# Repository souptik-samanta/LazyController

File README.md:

# LazyController

A compact WiFi-enabled relay controller built on a custom PCB. Flip switches, trigger appliances, and automate stuff — all from your phone or browser. No getting up required.

---
BUILD

## What is it?

LazyController is an IoT relay board designed around an ESP-based microcontroller. It exposes relay outputs over WiFi, letting you remotely toggle lights, fans, pumps, or anything else you'd rather not walk over to.

- Custom PCB with onboard relay(s)
- WiFi control via a web interface or serial commands
- Compact form factor — designed to tuck away somewhere tidy
- Production-ready Gerbers included for ordering straight from JLCPCB/PCBWay

---

## Repository Layout

```
LazyController/
├── Cad/          # Enclosure and assembly CAD files
├── Code/         # Firmware source (code.ino)
├── lib/          # README images/assets
├── Pcb/          # KiCad project files (schematic + PCB)
├── production/   # Manufacturing outputs (BOM, positions, netlist, backups)
└── README.md
```

---

## PCB

The board was designed with simplicity in mind — power in, relay out, WiFi in the middle.

> PCB layout and schematic are in the `Pcb/` folder.  
> Gerbers for direct upload to your fab of choice are in `production/`.

Ordering a board:
1. Zip the contents of `production/`
2. Upload to [JLCPCB](https://jlcpcb.com) or [PCBWay](https://www.pcbway.com)
3. Default settings (1.6mm, HASL, FR4) work fine

---
# Schematic

### ESP

<details>
   <summary><strong>USB</strong></summary>
   
</details>

<details>
   <summary><strong>Switching</strong></summary>
   
</details>

<details>
   <summary><strong>ACDC</strong></summary>
   
</details>

<details>
   <summary><strong>POWER</strong></summary>
   
</details>

## Flashing Firmware

> Make sure you have the [Arduino IDE](https://www.arduino.cc/en/software) or [PlatformIO](https://platformio.org) installed.

1. Add ESP32 board support if you haven't already:
   - In Arduino IDE → Preferences → Additional Board URLs:
     ```
     https://espressif.github.io/arduino-esp32/package_esp32_index.json
     ```
2. Install required libraries:
   - `ESPWiFi` (or `WiFi` for ESP32)
   - `ESPAsyncWebServer` *(recommended)*
3. Open your firmware sketch, set your WiFi credentials:
   ```cpp
   const char* ssid     = "your_network";
   const char* password = "your_password";
   ```
4. Select your board, plug in via USB, and hit **Upload**
5. Open Serial Monitor at `115200 baud` — it'll print the device IP once connected

---

## Wiring

```
Power the controller → relays get activated → each relay switches its connected load.
```

Relay outputs are SPDT — connect your load between **COM** and **NO** (normally open) for off-by-default behaviour.

> If switching mains voltage (120V/230V AC), make sure you take appropriate safety precautions. 

---

## Usage

Once flashed and powered:

1. Connect to the same WiFi network
2. Open a browser and navigate to the IP shown in Serial Monitor
3. Toggle relays from the web UI — or send HTTP requests directly:
   ```
   GET /relay/1/on
   GET /relay/1/off
   ```

---

## BOM

| NAME | DESC | QUAN | PRICE (USD) | PRICE TOT | LINK |
| --- | --- | ---: | ---: | ---: | --- |
| AC DC HLK 10M05 |  | 1 | 3 | 3 | [Link](https://www.google.com/aclk?sa=L&ai=DChsSEwjPgJLYkqGTAxU3E3sHHbncDPEYACICCAEQBhoCdG0&co=1&ase=2&gclid=CjwKCAjwjtTNBhB0EiwAuswYhhi3KHJIBAfwGXL-EoLnVRphFNGoqQidNDPKgIrQrcWKpcyjFP1VwBoCSCgQAvD_BwE&cid=CAASugHkaCU4e1fTz91kIGVNTnMzHJ_VtP52cufw6JcAMd-wP2ZSC0BoTFjcM9-ZIEFZ2Ogk6CTtzVucR90V1M1RdjyK8HSMxB6BEAwHAFI-Qtww65Lwu8Fu6KI2zU4457GgK06UIFovm7KTyVTxhy48PClOoNt_d_CozoYxK3R0wXO_8_H_BQkMjDaVLeeHGUlEV7Eb_OuckPo7iFx0EI2Cnf5IhQow1eqdLKqXXLbz55rZELgi1aYbH8s2oEE&cce=2&category=acrcp_v1_32&sig=AOD64_3fvvBr-_NRkMTrQTSOe75uZZv-rw&ctype=5&q=&nis=4&ved=2ahUKEwjd_4nYkqGTAxVSaPUHHT2JI8IQ9aACKAB6BAgLEA8&adurl=) |
| 6 Pin 5.08mm Pitch Pluggable Screw Terminal Block |  | 1 | 1 | 1 | [Link](https://robu.in/product/6-pin-5-08mm-pitch-pluggable-screw-terminal-block-pack-of-3/?gad_source=1&gad_campaignid=17427802703&gbraid=0AAAAADvLFWdwdvSUFSJIl7gt4S3iz58C-&gclid=CjwKCAjwjtTNBhB0EiwAuswYhp7bcND74BjkuenRPwyCr11HA-Sdw3UXYKsvjuJCSPtey4QP6JC4nhoCA68QAvD_BwE) |
| RELAY |  | 4 | 1 | 4 | [Link](https://robu.in/product/srd-5vdc-sl-a-ningbo-songle-relay-250vac-5v-15a-1-form-a-1a-spst-no-plugin15-6x19-2mm-power-relays-rohs/) |
| pcb |  | 23 | 1 | 23 |  |
| LCSC |  |  |  |  |  |
| CC0805JRNPO9BN471 | Description | 100 | 0.0074 | 0.74 | [Link](https://www.lcsc.com/product-detail/C62771.html) |
| CL21A225KBQNNNE | 470pF ±5% 50V Ceramic Capacitor NP0 0805 | 10 | 0.0176 | 0.176 | [Link](https://www.lcsc.com/product-detail/C377773.html) |
| GRM21BR61H106KE43L | 2.2uF ±10% 50V Ceramic Capacitor X5R 0805 | 10 | 0.0723 | 0.723 | [Link](https://www.lcsc.com/product-detail/C440198.html) |
| CC0603KRX7R9BB104 | 10uF ±10% 50V Ceramic Capacitor X5R 0805 | 100 | 0.0028 | 0.28 | [Link](https://www.lcsc.com/product-detail/C14663.html) |
| 1N5819W | 100nF ±10% 50V Ceramic Capacitor X7R 0603 | 100 | 0.0072 | 0.72 | [Link](https://www.lcsc.com/product-detail/C963381.html) |
| TYPE-C 16PIN 2MD(073) | Diode Independent 40V 350mA Surface Mount SOD-123 | 20 | 0.0617 | 1.234 | [Link](https://www.lcsc.com/product-detail/C2765186.html) |
| BC547 | USB-C (USB TYPE-C) Receptacle Connector 16 Position Surface Mount, Right Angle | 20 | 0.0302 | 0.604 | [Link](https://www.lcsc.com/product-detail/C47089404.html) |
| FRC0603F5101TS | Bipolar (BJT) Transistor NPN 45V 0.1A 150MHz 625mW Through Hole TO-92 | 100 | 0.0012 | 0.12 | [Link](https://www.lcsc.com/product-detail/C2907044.html) |
| RC0603FR-0710KL | 5.1kΩ ±1% 100mW 0603 Thick Film Resistor | 100 | 0.0013 | 0.13 | [Link](https://www.lcsc.com/product-detail/C98220.html) |
| RC0603FR-071KL | 100mW 10kΩ 75V Thick Film Resistor ±100ppm/℃ ±1% 0603 Chip Resistor - Surface Mount RoHS | 100 | 0.0013 | 0.13 | [Link](https://www.lcsc.com/product-detail/C22548.html) |
| SKRKAEE020 | 100mW 1kΩ 75V Thick Film Resistor ±100ppm/℃ ±1% 0603 Chip Resistor - Surface Mount RoHS | 5 | 0.1309 | 0.6545 | [Link](https://www.lcsc.com/product-detail/C115357.html) |
| ESP32-C3-WROOM-02-N4 | Tactile Switch SPST 2mm 3.9mm x 2.9mm Surface Mount | 1 | 3.0674 | 3.0674 | [Link](https://www.lcsc.com/product-detail/C2934560.html) |
| AMS1117-3.3 | 2.4GHz ESP32-C3 Chip On-board PCB Antenna -105dBm VFQFN-32-EP RF Transceiver Modules and Modems RoHS | 5 | 0.2259 | 1.1295 | [Link](https://www.lcsc.com/product-detail/C6186.html) |
|  | 3.3V 15V Positive Fixed SOT-223 Voltage Regulators - Linear, Low Drop Out (LDO) Regulators RoHS |  |  |  |  |
|  |  |  |  |  |  |
|  |  | TOTAL |  | 50.7084 |  |

- Full BOM sheet: [Open Google Sheet](https://docs.google.com/spreadsheets/d/1Jlhe0WWFfPgNdCmWaUOwISSQ84eng0tOMz2COa2eSn8/edit?usp=sharing)

## YouTube
- [Project video](https://youtu.be/daNDijgMs3k)
- More videos soon.

## Contact
- Email: [me@souptik.me](mailto:me@souptik.me)
- Slack: @Souptik Samanta

## Funding / Support
- Blueprint
- HackClub
---

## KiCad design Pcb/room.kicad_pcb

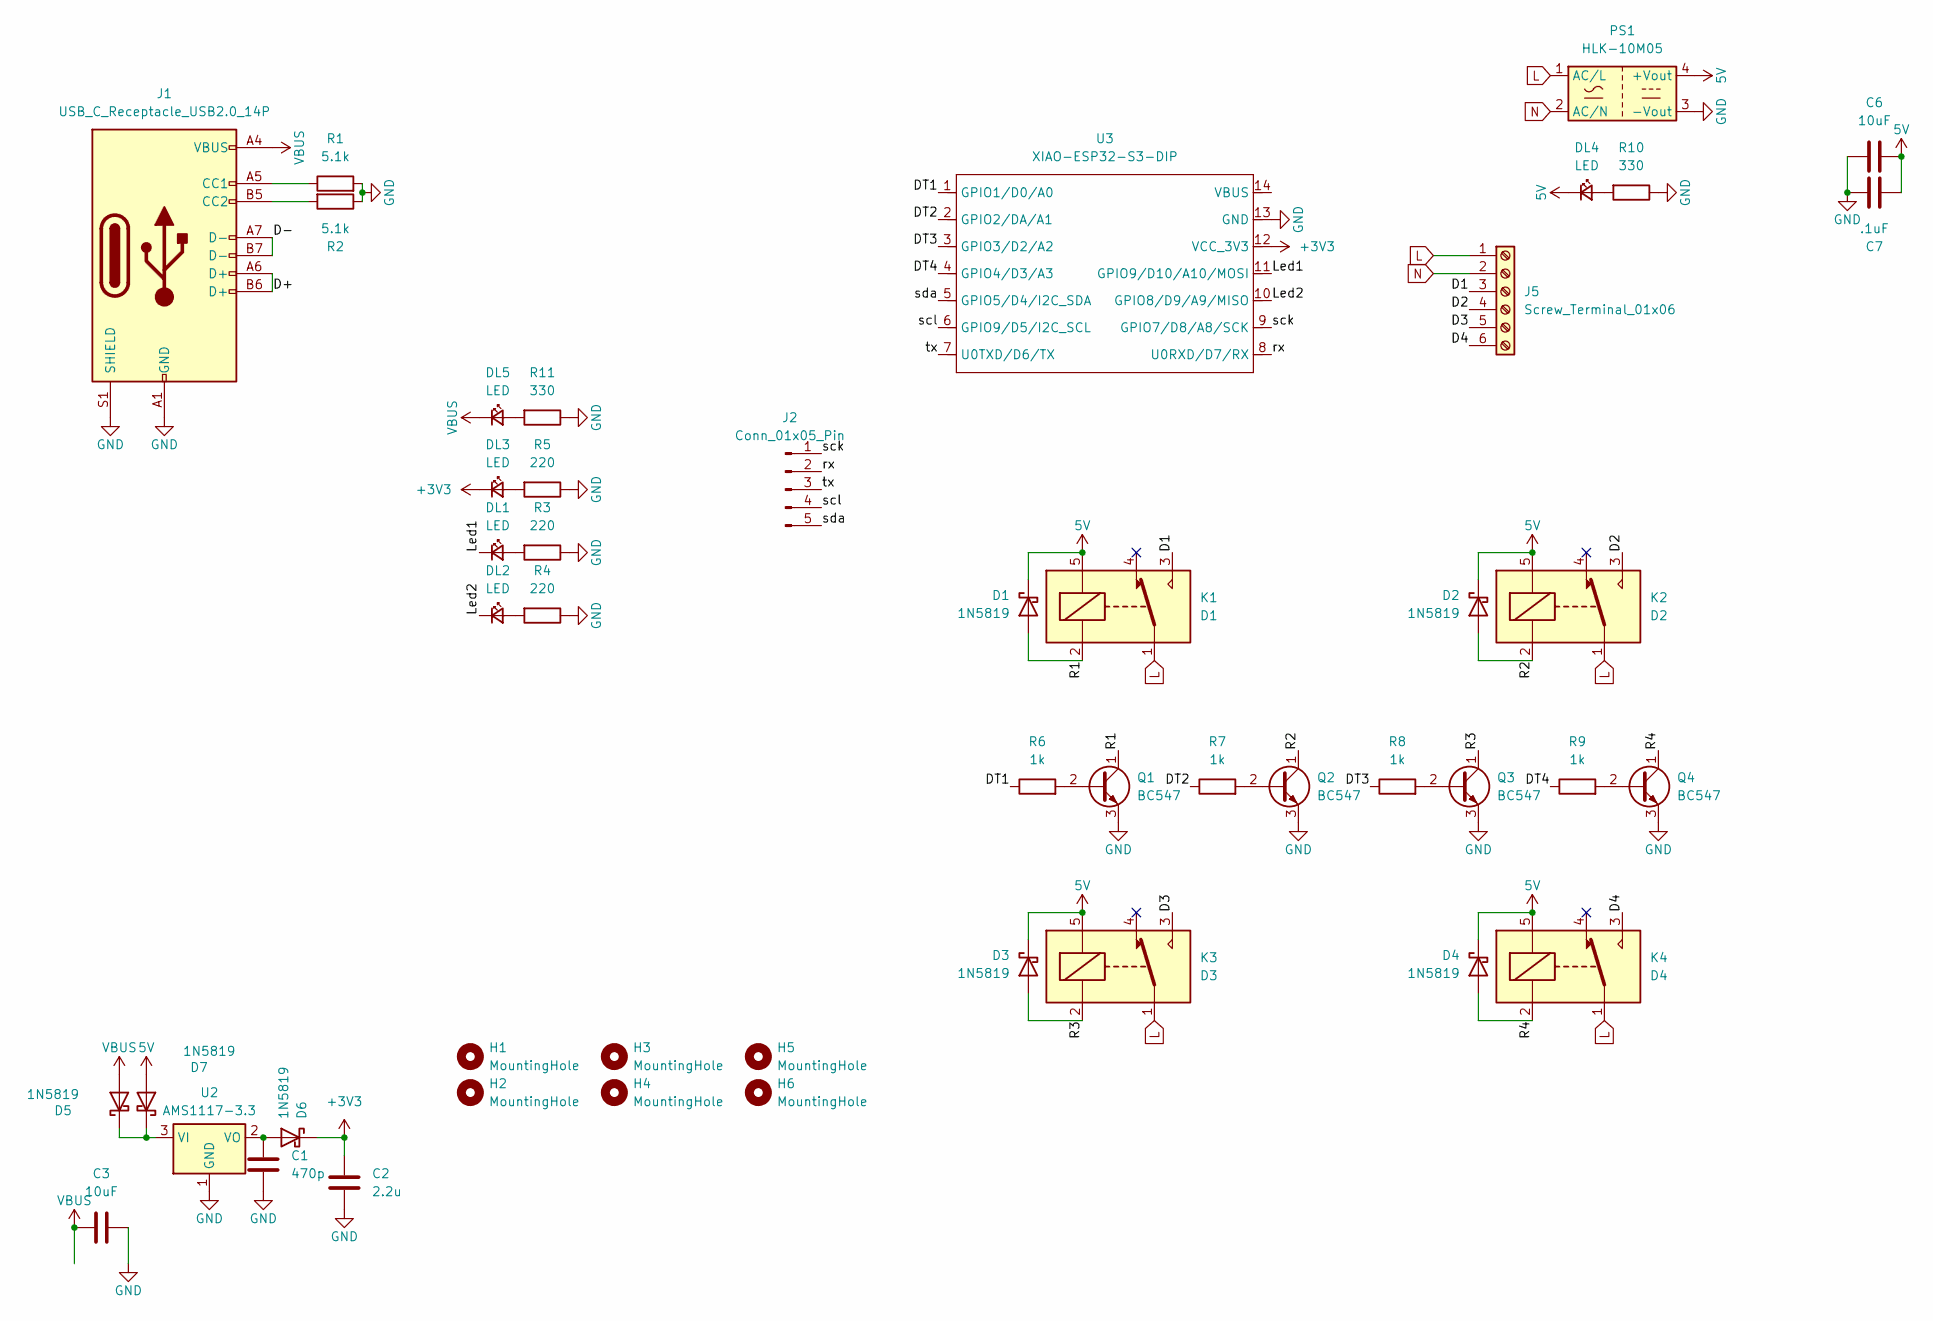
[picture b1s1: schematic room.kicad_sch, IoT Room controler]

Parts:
C1: 470p; C_0805_2012Metric
C2: 2.2u; C_0805_2012Metric
C3, C6: 10uF; C_0805_2012Metric
C7: .1uF; C_0603_1608Metric_Pad1.08x0.95mm_HandSolder
D1, D2, D3, D4, D5, D6, D7: 1N5819; D_SOD-123
DL1, DL2, DL3, DL4, DL5: LED; LED_0805_2012Metric_Pad1.15x1.40mm_HandSolder
H1, H2, H3, H4, H5, H6: MountingHole; MountingHole_2.5mm
J1: USB_C_Receptacle_USB2.0_14P; USB_C_Receptacle_GCT_USB4105-xx-A_16P_TopMnt_Horizontal
J2: Conn_01x05_Pin; PinHeader_1x05_P2.54mm_Vertical
J5: Screw_Terminal_01x06; TerminalBlock_bornier-6_P5.08mm
K1: D1; Relay_SPDT_SANYOU_SRD_Series_Form_C
K2: D2; Relay_SPDT_SANYOU_SRD_Series_Form_C
K3: D3; Relay_SPDT_SANYOU_SRD_Series_Form_C
K4: D4; Relay_SPDT_SANYOU_SRD_Series_Form_C
PS1: HLK-10M05; Converter_ACDC_Hi-Link_HLK-10Mxx
Q1, Q2, Q3, Q4: BC547; TO-92_Inline
R1, R2: 5.1k; R_0603_1608Metric
R3, R4, R5: 220; R_0603_1608Metric
R6, R7, R8, R9: 1k; R_0603_1608Metric
R10, R11: 330; R_0603_1608Metric
U2: AMS1117-3.3; SOT-223-3_TabPin2
U3: XIAO-ESP32-S3-DIP; XIAO-ESP32S3-DIP

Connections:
5V: C6.2, C7.1, D1.1 (K), D2.1 (K), D3.1 (K), D4.1 (K), D7.2 (A), DL4.1 (K), K1.5, K2.5, K3.5, K4.5, PS1.4 (+Vout)
+3V3: C2.1, D6.1 (K), DL3.1 (K), U3.12 (VCC_3V3)
/D1: J5.3, K1.3
/D2: J5.4, K2.3
/D3: J5.5, K3.3
/D4: J5.6, K4.3
/D+: J1.A6 (D+), J1.B6 (D+)
/D-: J1.A7 (D-), J1.B7 (D-)
/DT1: R6.1, U3.1 (GPIO1/D0/A0)
/DT2: R7.1, U3.2 (GPIO2/DA/A1)
/DT3: R8.1, U3.3 (GPIO3/D2/A2)
/DT4: R9.1, U3.4 (GPIO4/D3/A3)
/Led1: DL1.1 (K), U3.11 (GPIO9/D10/A10/MOSI)
/Led2: DL2.1 (K), U3.10 (GPIO8/D9/A9/MISO)
/R1: D1.2 (A), K1.2, Q1.1 (C)
/R2: D2.2 (A), K2.2, Q2.1 (C)
/R3: D3.2 (A), K3.2, Q3.1 (C)
/R4: D4.2 (A), K4.2, Q4.1 (C)
/rx: J2.2, U3.8 (U0RXD/D7/RX)
/sck: J2.1, U3.9 (GPIO7/D8/A8/SCK)
/scl: J2.4, U3.6 (GPIO9/D5/I2C_SCL)
/sda: J2.5, U3.5 (GPIO5/D4/I2C_SDA)
/tx: J2.3, U3.7 (U0TXD/D6/TX)
GND: C1.2, C2.2, C3.2, C6.1, C7.2, J1.A1 (GND), J1.A12 (GND), J1.B1 (GND), J1.B12 (GND), J1.S1 (SHIELD), PS1.3 (-Vout), Q1.3 (E), Q2.3 (E), Q3.3 (E), Q4.3 (E), R1.2, R2.1, R3.1, R4.1, R5.1, R10.1, R11.1, U2.1 (GND), U3.13 (GND)
L: J5.1, K1.1, K2.1, K3.1, K4.1, PS1.1 (AC/L)
N: J5.2, PS1.2 (AC/N)
unnamed: D5.1 (K), D7.1 (K), U2.3 (VI)
unnamed: C1.1, D6.2 (A), U2.2 (VO)
unnamed: DL1.2 (A), R3.2
unnamed: DL2.2 (A), R4.2
unnamed: DL3.2 (A), R5.2
unnamed: DL4.2 (A), R10.2
unnamed: DL5.2 (A), R11.2
unnamed: J1.A5 (CC1), R1.1
unnamed: J1.B5 (CC2), R2.2
unnamed: Q1.2 (B), R6.2
unnamed: Q2.2 (B), R7.2
unnamed: Q3.2 (B), R8.2
unnamed: Q4.2 (B), R9.2
VBUS: C3.1, D5.2 (A), DL5.1 (K), J1.A4 (VBUS), J1.A9 (VBUS), J1.B4 (VBUS), J1.B9 (VBUS)

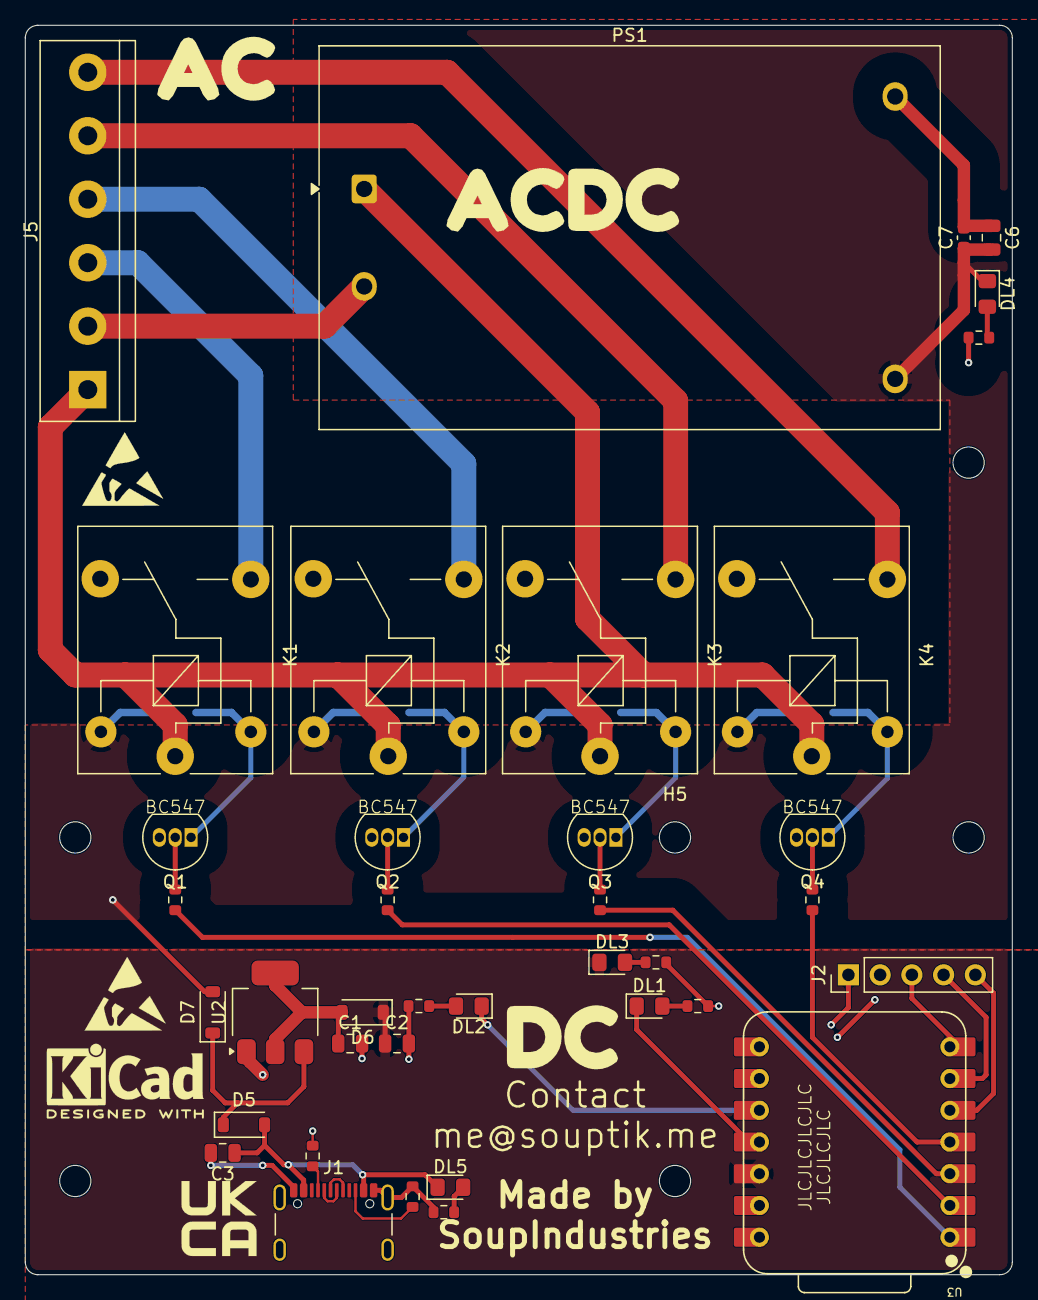
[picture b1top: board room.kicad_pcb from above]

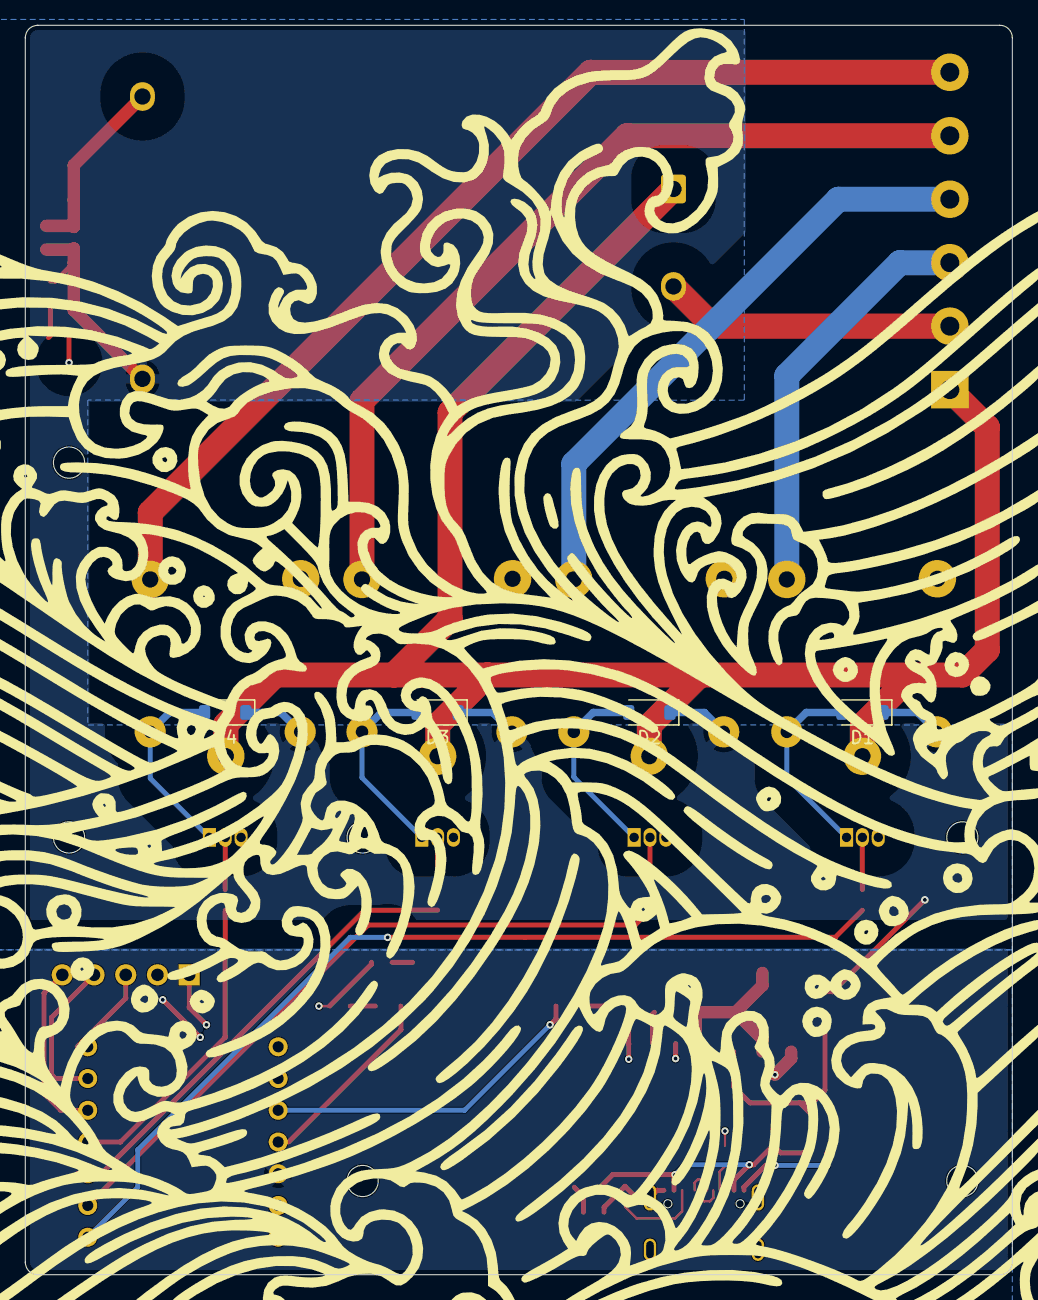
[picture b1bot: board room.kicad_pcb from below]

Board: 4 copper layers, 79.0 x 100.0 mm, 51 parts (4 on the bottom side), 40 nets.

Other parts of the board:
kibuzzard-69B63945: G***; kibuzzard-69B63945
kibuzzard-69B63969: G***; kibuzzard-69B63969
kibuzzard-69C64D69: G***; kibuzzard-69C64D69

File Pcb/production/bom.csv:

Designator,Footprint,Quantity,Value,LCSC Part #
C1,0805,1,470p,
C2,0805,1,2.2u,
"C3, C6",0805,2,10uF,
C7,0603,1,.1uF,
"D1, D2, D3, D4, D5, D6, D7",D_SOD-123,7,1N5819,
"DL1, DL2, DL3, DL4, DL5",0805,5,LED,
J1,USB_C_Receptacle_GCT_USB4105-xx-A_16P_TopMnt_Horizontal,1,USB_C_Receptacle_USB2.0_14P,
J2,PinHeader_1x05_P2.54mm_Vertical,1,Conn_01x05_Pin,
J5,TerminalBlock_bornier-6_P5.08mm,1,Screw_Terminal_01x06,
K1,Relay_SPDT_SANYOU_SRD_Series_Form_C,1,D1,
K2,Relay_SPDT_SANYOU_SRD_Series_Form_C,1,D2,
K3,Relay_SPDT_SANYOU_SRD_Series_Form_C,1,D3,
K4,Relay_SPDT_SANYOU_SRD_Series_Form_C,1,D4,
PS1,Converter_ACDC_Hi-Link_HLK-10Mxx,1,HLK-10M05,
"Q1, Q2, Q3, Q4",TO-92_Inline,4,BC547,
"R1, R2",0603,2,5.1k,
"R10, R11",0603,2,330,
"R3, R4, R5",0603,3,220,
"R6, R7, R8, R9",0603,4,1k,
U2,SOT-223-3_TabPin2,1,AMS1117-3.3,
U3,XIAO-ESP32S3-DIP,1,XIAO-ESP32-S3-DIP,

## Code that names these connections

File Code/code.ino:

/*
  LazyController — 4 Relay WiFi Controller
  MCU: ESP32-C3-WROOM-02
  Transistors: BC547 (NPN, active HIGH)
  
  Relay GPIOs — adjust to match your PCB traces:
  Relay 1 → GPIO2
  Relay 2 → GPIO3
  Relay 3 → GPIO4
  Relay 4 → GPIO5
*/

#include <WiFi.h>
#include <WebServer.h>

// ─── Config ───────────────────────────────────────────────
const char* SSID     = "your_wifi_ssid";
const char* PASSWORD = "your_wifi_password";

const int RELAY_PINS[4] = {2, 3, 4, 5};  // adjust if needed
bool relayState[4]      = {false, false, false, false};

WebServer server(80);

// ─── HTML UI ──────────────────────────────────────────────
const char INDEX_HTML[] PROGMEM = R"rawliteral(
<!DOCTYPE html>
<html>
<head>
  <meta charset="UTF-8">
  <meta name="viewport" content="width=device-width, initial-scale=1">
  <title>LazyController</title>
  <style>
    * { box-sizing: border-box; margin: 0; padding: 0; }
    body {
      font-family: monospace;
      background: #0f0f0f;
      color: #e0e0e0;
      display: flex;
      flex-direction: column;
      align-items: center;
      min-height: 100vh;
      padding: 40px 16px;
    }
    h1 { font-size: 1.4rem; letter-spacing: 0.15em; color: #fff; margin-bottom: 6px; }
    p.sub { font-size: 0.75rem; color: #555; margin-bottom: 40px; }
    .grid { display: grid; grid-template-columns: 1fr 1fr; gap: 16px; width: 100%; max-width: 380px; }
    .card {
      background: #1a1a1a;
      border: 1px solid #2a2a2a;
      border-radius: 12px;
      padding: 24px 16px;
      display: flex;
      flex-direction: column;
      align-items: center;
      gap: 14px;
    }
    .label { font-size: 0.7rem; color: #777; letter-spacing: 0.1em; text-transform: uppercase; }
    .dot {
      width: 12px; height: 12px;
      border-radius: 50%;
      background: #2a2a2a;
      box-shadow: 0 0 0 3px #1a1a1a;
      transition: background 0.2s, box-shadow 0.2s;
    }
    .dot.on { background: #00e676; box-shadow: 0 0 8px #00e676aa; }
    .btn {
      width: 100%;
      padding: 10px;
      border: none;
      border-radius: 8px;
      background: #222;
      color: #ccc;
      font-family: monospace;
      font-size: 0.8rem;
      cursor: pointer;
      transition: background 0.15s, color 0.15s;
      letter-spacing: 0.08em;
    }
    .btn:hover { background: #2e2e2e; color: #fff; }
    .btn.on { background: #00c853; color: #000; }
    .btn.on:hover { background: #00e676; }
    .all-row { display: flex; gap: 10px; width: 100%; max-width: 380px; margin-top: 24px; }
    .all-row .btn { flex: 1; }
  </style>
</head>
<body>
  <h1>LazyController</h1>
  <p class="sub">ESP32-C3 · 4 relay · WiFi</p>

  <div class="grid" id="grid"></div>

  <div class="all-row">
    <button class="btn" onclick="allRelays(true)">ALL ON</button>
    <button class="btn" onclick="allRelays(false)">ALL OFF</button>
  </div>

  <script>
    let states = [false, false, false, false];

    function buildUI() {
      const grid = document.getElementById('grid');
      grid.innerHTML = '';
      states.forEach((on, i) => {
        grid.innerHTML += `
          <div class="card">
            <div class="dot ${on ? 'on' : ''}" id="dot${i}"></div>
            <span class="label">Relay ${i + 1}</span>
            <button class="btn ${on ? 'on' : ''}" onclick="toggle(${i})">
              ${on ? 'ON' : 'OFF'}
            </button>
          </div>`;
      });
    }

    async function fetchStates() {
      const res = await fetch('/state');
      states = await res.json();
      buildUI();
    }

    async function toggle(i) {
      await fetch(`/relay/${i + 1}/${states[i] ? 'off' : 'on'}`);
      fetchStates();
    }

    async function allRelays(on) {
      await fetch(`/all/${on ? 'on' : 'off'}`);
      fetchStates();
    }

    fetchStates();
    setInterval(fetchStates, 3000);
  </script>
</body>
</html>
)rawliteral";

// ─── Handlers ─────────────────────────────────────────────
void handleRoot() {
  server.send(200, "text/html", INDEX_HTML);
}

void handleState() {
  String json = "[";
  for (int i = 0; i < 4; i++) {
    json += relayState[i] ? "true" : "false";
    if (i < 3) json += ",";
  }
  json += "]";
  server.send(200, "application/json", json);
}

void handleRelay() {
  // URL: /relay/{1-4}/{on|off}
  String uri = server.uri();  // e.g. /relay/2/on
  int relayNum = uri.charAt(7) - '0';  // char at index 7 = relay number
  bool turnOn  = uri.endsWith("on");

  if (relayNum >= 1 && relayNum <= 4) {
    int idx = relayNum - 1;
    relayState[idx] = turnOn;
    digitalWrite(RELAY_PINS[idx], turnOn ? HIGH : LOW);
    server.send(200, "text/plain", turnOn ? "on" : "off");
  } else {
    server.send(400, "text/plain", "bad relay number");
  }
}

void handleAll() {
  bool turnOn = server.uri().endsWith("on");
  for (int i = 0; i < 4; i++) {
    relayState[i] = turnOn;
    digitalWrite(RELAY_PINS[i], turnOn ? HIGH : LOW);
  }
  server.send(200, "text/plain", "ok");
}

// ─── Setup ────────────────────────────────────────────────
void setup() {
  Serial.begin(115200);

  // Init relay pins
  for (int i = 0; i < 4; i++) {
    pinMode(RELAY_PINS[i], OUTPUT);
    digitalWrite(RELAY_PINS[i], LOW);  // relays OFF on boot
  }

  // Connect WiFi
  Serial.printf("\nConnecting to %s", SSID);
  WiFi.begin(SSID, PASSWORD);
  while (WiFi.status() != WL_CONNECTED) {
    delay(500);
    Serial.print(".");
  }
  Serial.printf("\nConnected! IP: %s\n", WiFi.localIP().toString().c_str());

  // Routes
  server.on("/",          HTTP_GET, handleRoot);
  server.on("/state",     HTTP_GET, handleState);
  server.onNotFound([&]() {
    String uri = server.uri();
    if (uri.startsWith("/relay/")) handleRelay();
    else if (uri.startsWith("/all/"))  handleAll();
    else server.send(404, "text/plain", "not found");
  });

  server.begin();
  Serial.println("HTTP server started.");
}

// ─── Loop ─────────────────────────────────────────────────
void loop() {
  server.handleClient();
}

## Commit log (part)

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2026-03-12 okay
2026-03-15 Mostly done
2026-03-18 all done
2026-03-18 readme new linsk
2026-03-18 readme fix again lol
2026-03-18 readme schm pic add
2026-03-18 pics went to root lol
2026-06-05 Final update for pcb
2026-06-10 Add build image to README
    Added a build image to the README for visual reference.
2026-06-10 Resolve merge
